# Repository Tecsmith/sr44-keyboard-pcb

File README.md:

# SR44-Keyboard-PCB

## Intent

A macro-pad / num-pad cluster **companion** keyboard with QMK f/w, *for those who use 60%/70% keyboards but need a num-cluster*.  Also something for those extra key-caps to do.

## Layout ideation renders

#### Render

#### Layout

#### Matrix

## Planned Features

- [ ] QMK build
- [ ] MCU `RP2350` *(Depending on QMK support.  Keep track: [#24346](https://github.com/qmk/qmk_firmware/pull/24346) )s*
- [ ] C3/4 UDB Usb-C
- [ ] Hotswap MX ~~or Choc~~ switches ~~*(dual support. MAYBE NOT)*~~ *<small>[Hotswap dual not viable]</small>*
- [ ] 5 x positions for Skyloong Rotary Encoder *(with all 5 in concurrent use capability)*
- [ ] USB PD Sink controller for 5V-3A Power Delivery. `HUSB238` ~~*or*~~ ~~`TPS25730`~~ ~~*or*~~ ~~`STUSB4500`~~
- [ ] Built in USB-Hub, 3-port.  Two back, one on right side.  `CH334F`
  - with option to off-line the Hub but keep the KB working. Needs `TS3USB221`
- [ ] OLED Display screen module.
  - White *(a.k.a. 0.91-inch OLED)* *or* Color *(?? imposible to find)*
  - 128x32 resolution 
  - 19 x 33 mm (0.75 x 1.5 inch) &#177;Max size
- [ ] Battery backed-up RTC for time display. `DS1307`
- [ ] Temperature sensor. `DS18B20`
- [ ] All 2U keys have 2x 1U options *(hot-swap)*
- [ ] Additional optional keys around the arrow cluster
- [ ] `AST1109MLTRQ` buzzer.  *(For builtin alarm function, MAYBE?)*

## Wish List

- Add WiFi automation module *(for remote macro keypress, e.g. shutdown macro)*
  - [Tasmota](https://github.com/arendst/tasmota) on `ESP8684-WROOM-02C`/`-02UC` *(a.k.a. [`ESP32-C2`](https://www.espressif.com/en/products/socs/esp32-c2))*
  - *or*, [ShellyX](https://x.shelly.com/)

## Possible BIG issues

- Stacking the electronics features - may not have space on the PCB
- `RP2350` not on ChBios yet, so not on QMK

&nbsp;<br>&nbsp;

---
Made with :heart: by Silvino Rodrigues

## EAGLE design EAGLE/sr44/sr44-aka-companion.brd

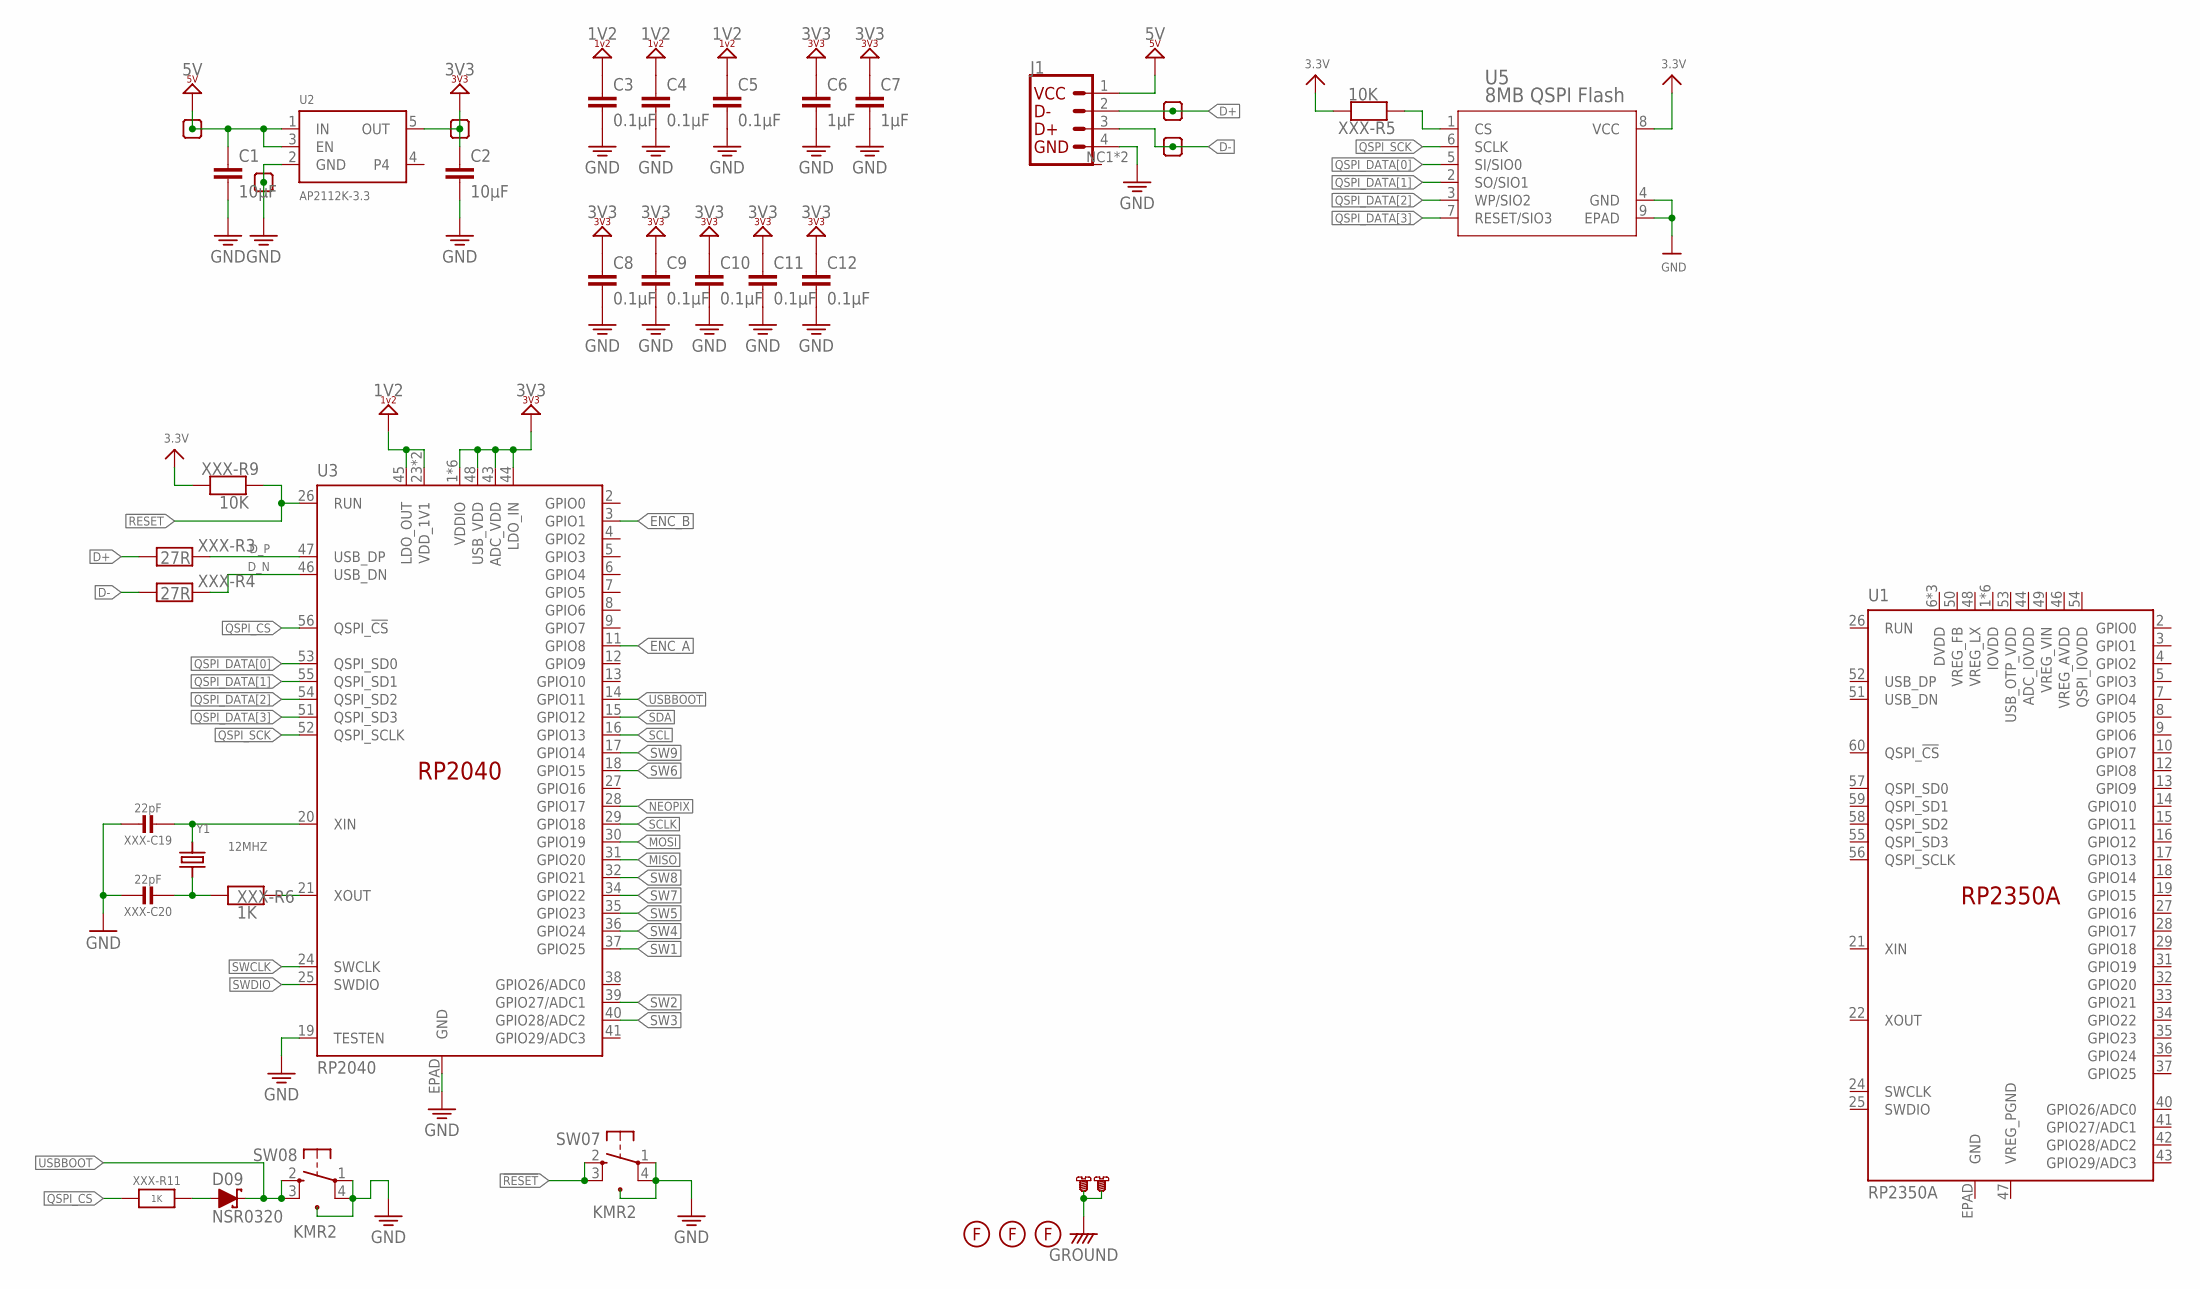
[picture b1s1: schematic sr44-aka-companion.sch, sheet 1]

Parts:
C1, C2: 10µF; C0603
C3, C4, C5, C8, C9, C10, C11, C12: 0.1µF; C0603
C6, C7: 1µF; C0603
D09: NSR0320; SOD-123
J1: UBD-S1_C4; MOLEX_781710004
SW07, SW08: KMR2; SW4_KMR221GLFS_CNK
TP1, TP2, TP3, TP4, TP5: TEST-POINT.3RN; PAD.03X.03-RN
U1: RP2350A; QFN-60
U2: AP2112K-3.3; SOT23-5
U3: RP2040; QFN-56
U5: 8MB QSPI Flash; USON-8L-2X3X0P6_MAC-M
U$44, U$51: MOUNTING-HOLE-2.2
U$54, U$55, U$56: FIDUCIAL
XXX-C19, XXX-C20: 22pF; _0402NO
XXX-R3, XXX-R4: 27R; _0402NO
XXX-R5, XXX-R9: 10K; _0402NO
XXX-R6, XXX-R11: 1K; _0402NO
Y1: 12MHZ; CRYSTAL_2.5X2

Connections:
3.3V: U5.8 (VCC), XXX-R5.2, XXX-R9.1
!RESET: SW07.2, SW07.3, U3.26 (RUN), XXX-R9.2
D+: J1.2 (DN), TP1.1, XXX-R3.2
D-: J1.3 (DP), TP2.1, XXX-R4.2
D_N: U3.46 (USB_DN), XXX-R4.1
D_P: U3.47 (USB_DP), XXX-R3.1
ENC_A: U3.11 (GPIO8)
ENC_B: U3.3 (GPIO1)
GND: C1.2, C2.2, C3.2, C4.2, C5.2, C6.2, C7.2, C8.2, C9.2, C10.2, C11.2, C12.2, J1.4 (GND), SW07.1, SW07.4, SW07.5, SW08.1, SW08.4, SW08.5, TP5.1, U2.2 (GND), U3.19 (TESTEN), U3.EPAD (GND), U5.4 (GND), U5.9 (EPAD), XXX-C19.1, XXX-C20.1; also elsewhere on the board
GROUND: U$44.P$1@1, U$44.P$1@2, U$44.P$1@3, U$44.P$1@4, U$44.P$1@5, U$44.P$1@6, U$51.P$1@1, U$51.P$1@2, U$51.P$1@3, U$51.P$1@4, U$51.P$1@5, U$51.P$1@6
MISO: U3.31 (GPIO20)
MOSI: U3.30 (GPIO19)
unnamed: D09.A, XXX-R11.2
unnamed: U3.20 (XIN), XXX-C19.2, Y1.3 (2)
unnamed: XXX-C20.2, XXX-R6.1, Y1.1
unnamed: U3.21 (XOUT), XXX-R6.2
NEOPIX: U3.28 (GPIO17)
QSPI_CS: U3.56 (QSPI_!CS!), U5.1 (CS), XXX-R5.1, XXX-R11.1
QSPI_DATA[0]: U3.53 (QSPI_SD0), U5.5 (SI/SIO0)
QSPI_DATA[1]: U3.55 (QSPI_SD1), U5.2 (SO/SIO1)
QSPI_DATA[2]: U3.54 (QSPI_SD2), U5.3 (WP/SIO2)
QSPI_DATA[3]: U3.51 (QSPI_SD3), U5.7 (RESET/SIO3)
QSPI_SCK: U3.52 (QSPI_SCLK), U5.6 (SCLK)
SCL: U3.16 (GPIO13)
SCLK: U3.29 (GPIO18)
SDA: U3.15 (GPIO12)
SW1: U3.37 (GPIO25)
SW2: U3.39 (GPIO27/ADC1)
SW3: U3.40 (GPIO28/ADC2)
SW4: U3.36 (GPIO24)
SW5: U3.35 (GPIO23)
SW6: U3.18 (GPIO15)
SW7: U3.34 (GPIO22)
SW8: U3.32 (GPIO21)
SW9: U3.17 (GPIO14)
SWCLK: U3.24 (SWCLK)
SWDIO: U3.25 (SWDIO)
USBBOOT: D09.C, SW08.2, SW08.3, U3.14 (GPIO11)
VCC2: C3.1, C4.1, C5.1, U3.23 (VDD_1V1), U3.45 (LDO_OUT), U3.50 (VDD_1V1)
VCC3: C2.1, C6.1, C7.1, C8.1, C9.1, C10.1, C11.1, C12.1, TP4.1, U2.5 (OUT), U3.1 (VDDIO), U3.10 (VDDIO), U3.22 (VDDIO), U3.33 (VDDIO), U3.42 (VDDIO), U3.43 (ADC_VDD), U3.44 (LDO_IN), U3.48 (USB_VDD), U3.49 (VDDIO)
VCC5: C1.1, J1.1 (VCC), TP3.1, U2.1 (IN), U2.3 (EN); also elsewhere on the board

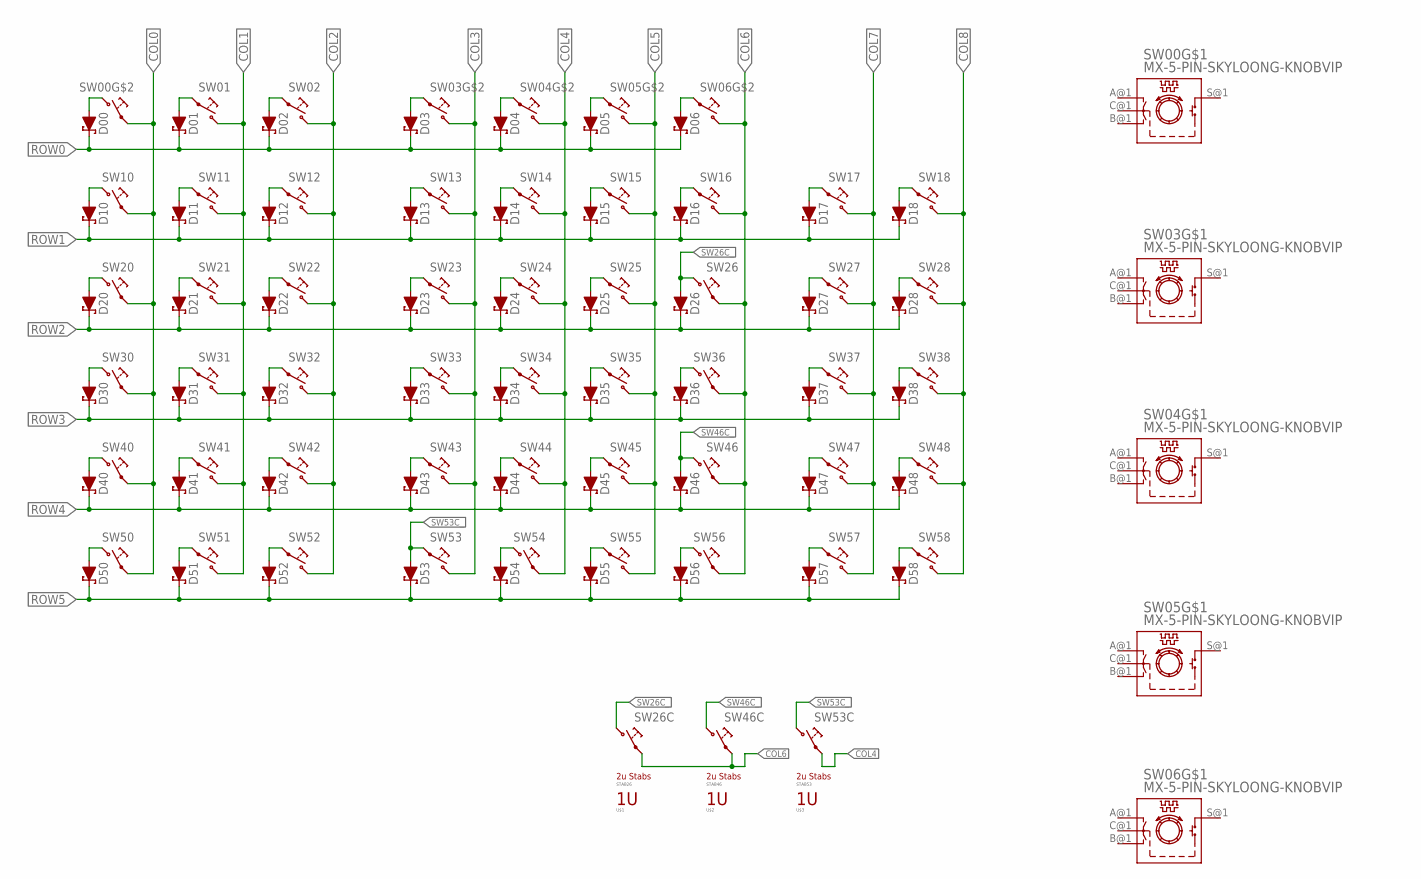
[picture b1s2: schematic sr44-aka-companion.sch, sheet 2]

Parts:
D00, D01, D02, D03, D04, D05, D06, D10, D11, D12, D13, D14, D15, D16, D17, D18, D20, D21, D22, D23, D24, D25, D26, D27, D28, D30, D31, D32, D33, D34, D35, D36, D37, D38, D40, D41, D42, D43, D44, D45, D46, D47, D48, D50, D51, D52, D53, D54, D55, D56, D57, D58: 1N5819WS; SOD-123
STAB26, STAB46, STAB53: MX-STABS-200U
SW00, SW03, SW04, SW05, SW06: MX-5-PIN-SKYLOONG-KNOBVIP; MX-5-PIN-SKYLOONG-KNOB-VIP
SW01, SW02, SW10, SW11, SW12, SW13, SW14, SW15, SW16, SW17, SW18, SW20, SW21, SW22, SW23, SW24, SW25, SW26, SW26C, SW27, SW28, SW30, SW31, SW32, SW33, SW34, SW35, SW36, SW37, SW38, SW40, SW41, SW42, SW43, SW44, SW45, SW46, SW46C, SW47, SW48, SW50, SW51, SW52, SW53, SW53C, SW54, SW55, SW56, SW57, SW58: MX-5-PIN-HOTSWAP-VIAVIP; MX-5-PIN-HOTSWAP-VIA+VIP-NS
U$1, U$2, U$3: MX-FPRINT-100U-PLACE; MX-FPRINT-PLACE-100U

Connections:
COL0: SW00.1@1 (1), SW00.1@2 (1), SW00.1@3 (1), SW10.1@1 (1), SW10.1@2 (1), SW10.1@3 (1), SW20.1@1 (1), SW20.1@2 (1), SW20.1@3 (1), SW30.1@1 (1), SW30.1@2 (1), SW30.1@3 (1), SW40.1@1 (1), SW40.1@2 (1), SW40.1@3 (1), SW50.1@1 (1), SW50.1@2 (1), SW50.1@3 (1)
COL1: SW01.2@1 (2), SW01.2@2 (2), SW01.2@3 (2), SW11.2@1 (2), SW11.2@2 (2), SW11.2@3 (2), SW21.2@1 (2), SW21.2@2 (2), SW21.2@3 (2), SW31.2@1 (2), SW31.2@2 (2), SW31.2@3 (2), SW41.2@1 (2), SW41.2@2 (2), SW41.2@3 (2), SW51.2@1 (2), SW51.2@2 (2), SW51.2@3 (2)
COL2: SW02.2@1 (2), SW02.2@2 (2), SW02.2@3 (2), SW12.2@1 (2), SW12.2@2 (2), SW12.2@3 (2), SW22.2@1 (2), SW22.2@2 (2), SW22.2@3 (2), SW32.2@1 (2), SW32.2@2 (2), SW32.2@3 (2), SW42.2@1 (2), SW42.2@2 (2), SW42.2@3 (2), SW52.2@1 (2), SW52.2@2 (2), SW52.2@3 (2)
COL3: SW03.2@1 (2), SW03.2@2 (2), SW03.2@3 (2), SW13.2@1 (2), SW13.2@2 (2), SW13.2@3 (2), SW23.2@1 (2), SW23.2@2 (2), SW23.2@3 (2), SW33.2@1 (2), SW33.2@2 (2), SW33.2@3 (2), SW43.2@1 (2), SW43.2@2 (2), SW43.2@3 (2), SW53.2@1 (2), SW53.2@2 (2), SW53.2@3 (2)
COL4: SW04.2@1 (2), SW04.2@2 (2), SW04.2@3 (2), SW14.2@1 (2), SW14.2@2 (2), SW14.2@3 (2), SW24.2@1 (2), SW24.2@2 (2), SW24.2@3 (2), SW34.2@1 (2), SW34.2@2 (2), SW34.2@3 (2), SW44.2@1 (2), SW44.2@2 (2), SW44.2@3 (2), SW53C.1@1 (1), SW53C.1@2 (1), SW53C.1@3 (1), SW54.1@1 (1), SW54.1@2 (1), SW54.1@3 (1)
COL5: SW05.2@1 (2), SW05.2@2 (2), SW05.2@3 (2), SW15.2@1 (2), SW15.2@2 (2), SW15.2@3 (2), SW25.2@1 (2), SW25.2@2 (2), SW25.2@3 (2), SW35.2@1 (2), SW35.2@2 (2), SW35.2@3 (2), SW45.2@1 (2), SW45.2@2 (2), SW45.2@3 (2), SW55.2@1 (2), SW55.2@2 (2), SW55.2@3 (2)
COL6: SW06.2@1 (2), SW06.2@2 (2), SW06.2@3 (2), SW16.2@1 (2), SW16.2@2 (2), SW16.2@3 (2), SW26.1@1 (1), SW26.1@2 (1), SW26.1@3 (1), SW26C.1@1 (1), SW26C.1@2 (1), SW26C.1@3 (1), SW36.1@1 (1), SW36.1@2 (1), SW36.1@3 (1), SW46.1@1 (1), SW46.1@2 (1), SW46.1@3 (1), SW46C.1@1 (1), SW46C.1@2 (1), SW46C.1@3 (1), SW56.1@1 (1), SW56.1@2 (1), SW56.1@3 (1)
COL7: SW17.2@1 (2), SW17.2@2 (2), SW17.2@3 (2), SW27.2@1 (2), SW27.2@2 (2), SW27.2@3 (2), SW37.2@1 (2), SW37.2@2 (2), SW37.2@3 (2), SW47.2@1 (2), SW47.2@2 (2), SW47.2@3 (2), SW57.2@1 (2), SW57.2@2 (2), SW57.2@3 (2)
COL8: SW18.2@1 (2), SW18.2@2 (2), SW18.2@3 (2), SW28.2@1 (2), SW28.2@2 (2), SW28.2@3 (2), SW38.2@1 (2), SW38.2@2 (2), SW38.2@3 (2), SW48.2@1 (2), SW48.2@2 (2), SW48.2@3 (2), SW58.2@1 (2), SW58.2@2 (2), SW58.2@3 (2)
unnamed: D00.A, SW00.2@1 (2), SW00.2@2 (2), SW00.2@3 (2)
unnamed: D01.A, SW01.1@1 (1), SW01.1@2 (1), SW01.1@3 (1)
unnamed: D02.A, SW02.1@1 (1), SW02.1@2 (1), SW02.1@3 (1)
unnamed: D55.A, SW55.1@1 (1), SW55.1@2 (1), SW55.1@3 (1)
unnamed: D54.A, SW54.2@1 (2), SW54.2@2 (2), SW54.2@3 (2)
unnamed: D56.A, SW56.2@1 (2), SW56.2@2 (2), SW56.2@3 (2)
unnamed: D28.A, SW28.1@1 (1), SW28.1@2 (1), SW28.1@3 (1)
unnamed: D36.A, SW36.2@1 (2), SW36.2@2 (2), SW36.2@3 (2)
unnamed: D03.A, SW03.1@1 (1), SW03.1@2 (1), SW03.1@3 (1)
unnamed: D04.A, SW04.1@1 (1), SW04.1@2 (1), SW04.1@3 (1)
unnamed: D05.A, SW05.1@1 (1), SW05.1@2 (1), SW05.1@3 (1)
unnamed: D06.A, SW06.1@1 (1), SW06.1@2 (1), SW06.1@3 (1)
unnamed: D16.A, SW16.1@1 (1), SW16.1@2 (1), SW16.1@3 (1)
unnamed: D15.A, SW15.1@1 (1), SW15.1@2 (1), SW15.1@3 (1)
unnamed: D14.A, SW14.1@1 (1), SW14.1@2 (1), SW14.1@3 (1)
unnamed: D13.A, SW13.1@1 (1), SW13.1@2 (1), SW13.1@3 (1)
unnamed: D12.A, SW12.1@1 (1), SW12.1@2 (1), SW12.1@3 (1)
unnamed: D11.A, SW11.1@1 (1), SW11.1@2 (1), SW11.1@3 (1)
unnamed: D10.A, SW10.2@1 (2), SW10.2@2 (2), SW10.2@3 (2)
unnamed: D27.A, SW27.1@1 (1), SW27.1@2 (1), SW27.1@3 (1)
unnamed: D37.A, SW37.1@1 (1), SW37.1@2 (1), SW37.1@3 (1)
unnamed: D47.A, SW47.1@1 (1), SW47.1@2 (1), SW47.1@3 (1)
unnamed: D57.A, SW57.1@1 (1), SW57.1@2 (1), SW57.1@3 (1)
unnamed: D58.A, SW58.1@1 (1), SW58.1@2 (1), SW58.1@3 (1)
unnamed: D48.A, SW48.1@1 (1), SW48.1@2 (1), SW48.1@3 (1)
unnamed: D17.A, SW17.1@1 (1), SW17.1@2 (1), SW17.1@3 (1)
unnamed: D18.A, SW18.1@1 (1), SW18.1@2 (1), SW18.1@3 (1)
unnamed: D38.A, SW38.1@1 (1), SW38.1@2 (1), SW38.1@3 (1)
unnamed: D45.A, SW45.1@1 (1), SW45.1@2 (1), SW45.1@3 (1)
unnamed: D44.A, SW44.1@1 (1), SW44.1@2 (1), SW44.1@3 (1)
unnamed: D43.A, SW43.1@1 (1), SW43.1@2 (1), SW43.1@3 (1)
unnamed: D33.A, SW33.1@1 (1), SW33.1@2 (1), SW33.1@3 (1)
unnamed: D34.A, SW34.1@1 (1), SW34.1@2 (1), SW34.1@3 (1)
unnamed: D35.A, SW35.1@1 (1), SW35.1@2 (1), SW35.1@3 (1)
unnamed: D25.A, SW25.1@1 (1), SW25.1@2 (1), SW25.1@3 (1)
unnamed: D24.A, SW24.1@1 (1), SW24.1@2 (1), SW24.1@3 (1)
unnamed: D23.A, SW23.1@1 (1), SW23.1@2 (1), SW23.1@3 (1)
unnamed: D20.A, SW20.2@1 (2), SW20.2@2 (2), SW20.2@3 (2)
unnamed: D30.A, SW30.2@1 (2), SW30.2@2 (2), SW30.2@3 (2)
unnamed: D40.A, SW40.2@1 (2), SW40.2@2 (2), SW40.2@3 (2)
unnamed: D50.A, SW50.2@1 (2), SW50.2@2 (2), SW50.2@3 (2)
unnamed: D21.A, SW21.1@1 (1), SW21.1@2 (1), SW21.1@3 (1)
unnamed: D22.A, SW22.1@1 (1), SW22.1@2 (1), SW22.1@3 (1)
unnamed: D31.A, SW31.1@1 (1), SW31.1@2 (1), SW31.1@3 (1)
unnamed: D32.A, SW32.1@1 (1), SW32.1@2 (1), SW32.1@3 (1)
unnamed: D42.A, SW42.1@1 (1), SW42.1@2 (1), SW42.1@3 (1)
unnamed: D41.A, SW41.1@1 (1), SW41.1@2 (1), SW41.1@3 (1)
unnamed: D51.A, SW51.1@1 (1), SW51.1@2 (1), SW51.1@3 (1)
unnamed: D52.A, SW52.1@1 (1), SW52.1@2 (1), SW52.1@3 (1)
ROW0: D00.C, D01.C, D02.C, D03.C, D04.C, D05.C, D06.C
ROW1: D10.C, D11.C, D12.C, D13.C, D14.C, D15.C, D16.C, D17.C, D18.C
ROW2: D20.C, D21.C, D22.C, D23.C, D24.C, D25.C, D26.C, D27.C, D28.C
ROW3: D30.C, D31.C, D32.C, D33.C, D34.C, D35.C, D36.C, D37.C, D38.C
ROW4: D40.C, D41.C, D42.C, D43.C, D44.C, D45.C, D46.C, D47.C, D48.C
ROW5: D50.C, D51.C, D52.C, D53.C, D54.C, D55.C, D56.C, D57.C, D58.C
SW26C_: D26.A, SW26.2@1 (2), SW26.2@2 (2), SW26.2@3 (2), SW26C.2@1 (2), SW26C.2@2 (2), SW26C.2@3 (2)
SW46C_: D46.A, SW46.2@1 (2), SW46.2@2 (2), SW46.2@3 (2), SW46C.2@1 (2), SW46C.2@2 (2), SW46C.2@3 (2)
SW53C_: D53.A, SW53.1@1 (1), SW53.1@2 (1), SW53.1@3 (1), SW53C.2@1 (2), SW53C.2@2 (2), SW53C.2@3 (2)

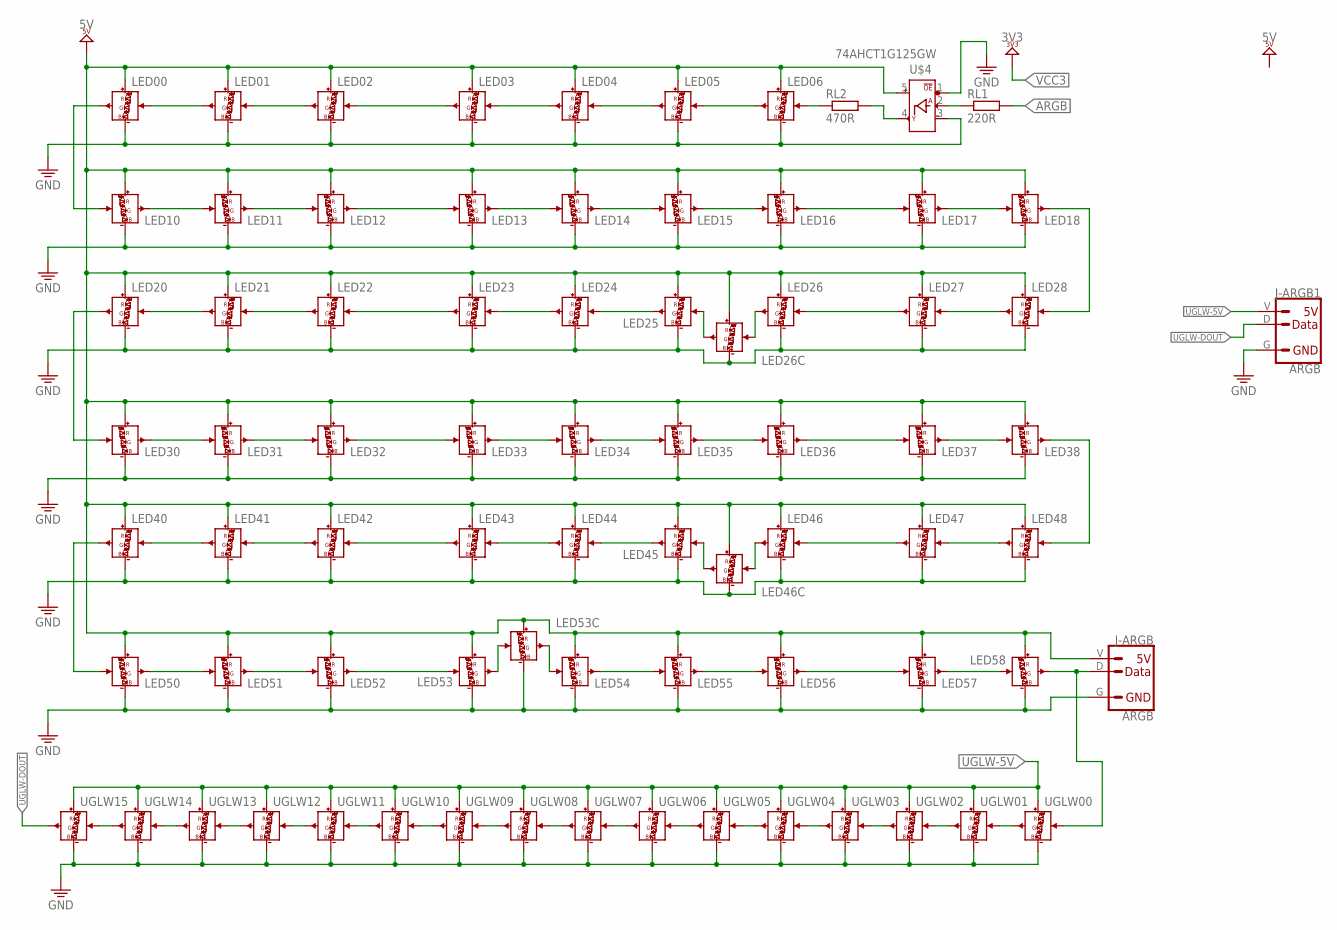
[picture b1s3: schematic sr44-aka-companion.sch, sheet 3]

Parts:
J-ARGB, J-ARGB1: ARGB
LED00, LED01, LED02, LED03, LED04, LED05, LED06, LED10, LED11, LED12, LED13, LED14, LED15, LED16, LED17, LED18, LED20, LED21, LED22, LED23, LED24, LED25, LED26, LED26C, LED27, LED28, LED30, LED31, LED32, LED33, LED34, LED35, LED36, LED37, LED38, LED40, LED41, LED42, LED43, LED44, LED45, LED46, LED46C, LED47, LED48, LED50, LED51, LED52, LED53, LED53C, LED54, LED55, LED56, LED57, LED58: SK6812-MINI-ESK6812MINI-E; SK6812-E-MILL_V2
RL1: 220R; R0603
RL2: 470R; R0603
U$4: 74AHCT1G125GW; SOT353
UGLW00, UGLW01, UGLW02, UGLW03, UGLW04, UGLW05, UGLW06, UGLW07, UGLW08, UGLW09, UGLW10, UGLW11, UGLW12, UGLW13, UGLW14, UGLW15: SK6812-MINISK6812MINI; SK6812_V2

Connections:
ARGB: RL1.2
GND: J-ARGB.G, J-ARGB1.G, LED00.3-GND (GND), LED01.3-GND (GND), LED02.3-GND (GND), LED03.3-GND (GND), LED04.3-GND (GND), LED05.3-GND (GND), LED06.3-GND (GND), LED10.3-GND (GND), LED11.3-GND (GND), LED12.3-GND (GND), LED13.3-GND (GND), LED14.3-GND (GND), LED15.3-GND (GND), LED16.3-GND (GND), LED17.3-GND (GND), LED18.3-GND (GND), LED20.3-GND (GND), LED21.3-GND (GND), LED22.3-GND (GND), LED23.3-GND (GND), LED24.3-GND (GND), LED25.3-GND (GND), LED26.3-GND (GND), LED26C.3-GND (GND), LED27.3-GND (GND), LED28.3-GND (GND), LED30.3-GND (GND), LED31.3-GND (GND), LED32.3-GND (GND), LED33.3-GND (GND), LED34.3-GND (GND), LED35.3-GND (GND), LED36.3-GND (GND), LED37.3-GND (GND), LED38.3-GND (GND), LED40.3-GND (GND), LED41.3-GND (GND), LED42.3-GND (GND), LED43.3-GND (GND), LED44.3-GND (GND), LED45.3-GND (GND), LED46.3-GND (GND), LED46C.3-GND (GND), LED47.3-GND (GND), LED48.3-GND (GND), LED50.3-GND (GND), LED51.3-GND (GND), LED52.3-GND (GND), LED53.3-GND (GND), LED53C.3-GND (GND), LED54.3-GND (GND), LED55.3-GND (GND), LED56.3-GND (GND), LED57.3-GND (GND), LED58.3-GND (GND), U$4.1 (!OE), U$4.3 (3_GND), UGLW00.4-GND (GND), UGLW01.4-GND (GND), UGLW02.4-GND (GND), UGLW03.4-GND (GND), UGLW04.4-GND (GND), UGLW05.4-GND (GND), UGLW06.4-GND (GND), UGLW07.4-GND (GND), UGLW08.4-GND (GND), UGLW09.4-GND (GND), UGLW10.4-GND (GND), UGLW11.4-GND (GND), UGLW12.4-GND (GND), UGLW13.4-GND (GND), UGLW14.4-GND (GND), UGLW15.4-GND (GND); also elsewhere on the board
unnamed: LED05.4-DIN (DIN), LED06.2-DOUT (DOUT)
unnamed: LED04.4-DIN (DIN), LED05.2-DOUT (DOUT)
unnamed: LED03.4-DIN (DIN), LED04.2-DOUT (DOUT)
unnamed: LED02.4-DIN (DIN), LED03.2-DOUT (DOUT)
unnamed: LED01.4-DIN (DIN), LED02.2-DOUT (DOUT)
unnamed: LED00.4-DIN (DIN), LED01.2-DOUT (DOUT)
unnamed: LED00.2-DOUT (DOUT), LED10.4-DIN (DIN)
unnamed: LED10.2-DOUT (DOUT), LED11.4-DIN (DIN)
unnamed: LED11.2-DOUT (DOUT), LED12.4-DIN (DIN)
unnamed: LED12.2-DOUT (DOUT), LED13.4-DIN (DIN)
unnamed: LED13.2-DOUT (DOUT), LED14.4-DIN (DIN)
unnamed: LED14.2-DOUT (DOUT), LED15.4-DIN (DIN)
unnamed: LED15.2-DOUT (DOUT), LED16.4-DIN (DIN)
unnamed: LED16.2-DOUT (DOUT), LED17.4-DIN (DIN)
unnamed: LED17.2-DOUT (DOUT), LED18.4-DIN (DIN)
unnamed: LED18.2-DOUT (DOUT), LED28.4-DIN (DIN)
unnamed: LED27.4-DIN (DIN), LED28.2-DOUT (DOUT)
unnamed: LED26.4-DIN (DIN), LED27.2-DOUT (DOUT)
unnamed: LED53.2-DOUT (DOUT), LED53C.4-DIN (DIN)
unnamed: LED24.4-DIN (DIN), LED25.2-DOUT (DOUT)
unnamed: LED23.4-DIN (DIN), LED24.2-DOUT (DOUT)
unnamed: LED22.4-DIN (DIN), LED23.2-DOUT (DOUT)
unnamed: LED21.4-DIN (DIN), LED22.2-DOUT (DOUT)
unnamed: LED20.4-DIN (DIN), LED21.2-DOUT (DOUT)
unnamed: LED20.2-DOUT (DOUT), LED30.4-DIN (DIN)
unnamed: LED30.2-DOUT (DOUT), LED31.4-DIN (DIN)
unnamed: LED31.2-DOUT (DOUT), LED32.4-DIN (DIN)
unnamed: LED32.2-DOUT (DOUT), LED33.4-DIN (DIN)
unnamed: LED33.2-DOUT (DOUT), LED34.4-DIN (DIN)
unnamed: LED34.2-DOUT (DOUT), LED35.4-DIN (DIN)
unnamed: LED35.2-DOUT (DOUT), LED36.4-DIN (DIN)
unnamed: LED36.2-DOUT (DOUT), LED37.4-DIN (DIN)
unnamed: LED37.2-DOUT (DOUT), LED38.4-DIN (DIN)
unnamed: LED38.2-DOUT (DOUT), LED48.4-DIN (DIN)
unnamed: LED47.4-DIN (DIN), LED48.2-DOUT (DOUT)
unnamed: LED26.2-DOUT (DOUT), LED26C.4-DIN (DIN)
unnamed: LED25.4-DIN (DIN), LED26C.2-DOUT (DOUT)
unnamed: LED46.4-DIN (DIN), LED47.2-DOUT (DOUT)
unnamed: LED44.4-DIN (DIN), LED45.2-DOUT (DOUT)
unnamed: LED43.4-DIN (DIN), LED44.2-DOUT (DOUT)
unnamed: LED42.4-DIN (DIN), LED43.2-DOUT (DOUT)
unnamed: LED41.4-DIN (DIN), LED42.2-DOUT (DOUT)
unnamed: LED40.4-DIN (DIN), LED41.2-DOUT (DOUT)
unnamed: LED40.2-DOUT (DOUT), LED50.4-DIN (DIN)
unnamed: LED50.2-DOUT (DOUT), LED51.4-DIN (DIN)
unnamed: LED51.2-DOUT (DOUT), LED52.4-DIN (DIN)
unnamed: LED52.2-DOUT (DOUT), LED53.4-DIN (DIN)
unnamed: LED53C.2-DOUT (DOUT), LED54.4-DIN (DIN)
unnamed: LED45.4-DIN (DIN), LED46C.2-DOUT (DOUT)
unnamed: LED54.2-DOUT (DOUT), LED55.4-DIN (DIN)
unnamed: LED55.2-DOUT (DOUT), LED56.4-DIN (DIN)
unnamed: LED56.2-DOUT (DOUT), LED57.4-DIN (DIN)
unnamed: LED57.2-DOUT (DOUT), LED58.4-DIN (DIN)
unnamed: UGLW02.3-DOUT (DOUT), UGLW03.1-DIN (DIN)
unnamed: UGLW01.3-DOUT (DOUT), UGLW02.1-DIN (DIN)
unnamed: UGLW00.3-DOUT (DOUT), UGLW01.1-DIN (DIN)
unnamed: UGLW03.3-DOUT (DOUT), UGLW04.1-DIN (DIN)
unnamed: UGLW04.3-DOUT (DOUT), UGLW05.1-DIN (DIN)
unnamed: UGLW05.3-DOUT (DOUT), UGLW06.1-DIN (DIN)
unnamed: UGLW06.3-DOUT (DOUT), UGLW07.1-DIN (DIN)
unnamed: UGLW07.3-DOUT (DOUT), UGLW08.1-DIN (DIN)
unnamed: UGLW08.3-DOUT (DOUT), UGLW09.1-DIN (DIN)
unnamed: UGLW09.3-DOUT (DOUT), UGLW10.1-DIN (DIN)
unnamed: UGLW10.3-DOUT (DOUT), UGLW11.1-DIN (DIN)
unnamed: LED46.2-DOUT (DOUT), LED46C.4-DIN (DIN)
unnamed: J-ARGB.D, LED58.2-DOUT (DOUT), UGLW00.1-DIN (DIN)
unnamed: UGLW11.3-DOUT (DOUT), UGLW12.1-DIN (DIN)
unnamed: LED06.4-DIN (DIN), RL2.1
unnamed: RL2.2, U$4.4 (Y_DOUT)
unnamed: RL1.1, U$4.2 (A_DIN)
unnamed: UGLW12.3-DOUT (DOUT), UGLW13.1-DIN (DIN)
unnamed: UGLW13.3-DOUT (DOUT), UGLW14.1-DIN (DIN)
unnamed: UGLW14.3-DOUT (DOUT), UGLW15.1-DIN (DIN)
UGLW-5V: J-ARGB1.V, UGLW00.2-VDD (VDD), UGLW01.2-VDD (VDD), UGLW02.2-VDD (VDD), UGLW03.2-VDD (VDD), UGLW04.2-VDD (VDD), UGLW05.2-VDD (VDD), UGLW06.2-VDD (VDD), UGLW07.2-VDD (VDD), UGLW08.2-VDD (VDD), UGLW09.2-VDD (VDD), UGLW10.2-VDD (VDD), UGLW11.2-VDD (VDD), UGLW12.2-VDD (VDD), UGLW13.2-VDD (VDD), UGLW14.2-VDD (VDD), UGLW15.2-VDD (VDD)
UGLW-DOUT: J-ARGB1.D, UGLW15.3-DOUT (DOUT)
VCC5: J-ARGB.V, LED00.1-VDD (VDD), LED01.1-VDD (VDD), LED02.1-VDD (VDD), LED03.1-VDD (VDD), LED04.1-VDD (VDD), LED05.1-VDD (VDD), LED06.1-VDD (VDD), LED10.1-VDD (VDD), LED11.1-VDD (VDD), LED12.1-VDD (VDD), LED13.1-VDD (VDD), LED14.1-VDD (VDD), LED15.1-VDD (VDD), LED16.1-VDD (VDD), LED17.1-VDD (VDD), LED18.1-VDD (VDD), LED20.1-VDD (VDD), LED21.1-VDD (VDD), LED22.1-VDD (VDD), LED23.1-VDD (VDD), LED24.1-VDD (VDD), LED25.1-VDD (VDD), LED26.1-VDD (VDD), LED26C.1-VDD (VDD), LED27.1-VDD (VDD), LED28.1-VDD (VDD), LED30.1-VDD (VDD), LED31.1-VDD (VDD), LED32.1-VDD (VDD), LED33.1-VDD (VDD), LED34.1-VDD (VDD), LED35.1-VDD (VDD), LED36.1-VDD (VDD), LED37.1-VDD (VDD), LED38.1-VDD (VDD), LED40.1-VDD (VDD), LED41.1-VDD (VDD), LED42.1-VDD (VDD), LED43.1-VDD (VDD), LED44.1-VDD (VDD), LED45.1-VDD (VDD), LED46.1-VDD (VDD), LED46C.1-VDD (VDD), LED47.1-VDD (VDD), LED48.1-VDD (VDD), LED50.1-VDD (VDD), LED51.1-VDD (VDD), LED52.1-VDD (VDD), LED53.1-VDD (VDD), LED53C.1-VDD (VDD), LED54.1-VDD (VDD), LED55.1-VDD (VDD), LED56.1-VDD (VDD), LED57.1-VDD (VDD), LED58.1-VDD (VDD), U$4.5 (5_VCC); also elsewhere on the board

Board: 4 copper layers, 228 parts (53 on the bottom side), 164 nets, no tracks yet.

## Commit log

2024-09-13 Initial upload
2024-09-24 render
2024-09-26 docs
2024-09-27 initial EAGLE placing

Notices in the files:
parts and their libraries:
microbuilder: This work is placed in the public domain, and may be freely used for commercial and non-commercial work with the following conditions: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
COPYRIGHT: Copyright (C) 2024 Ultra Librarian. All rights reserved.
